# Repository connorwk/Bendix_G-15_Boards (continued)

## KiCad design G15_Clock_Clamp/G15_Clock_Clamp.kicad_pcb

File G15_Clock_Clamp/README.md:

# Clock Clamp, For Bendix G-15 CPU
[Schematic](G15_Clock_Clamp_Schematic.pdf)

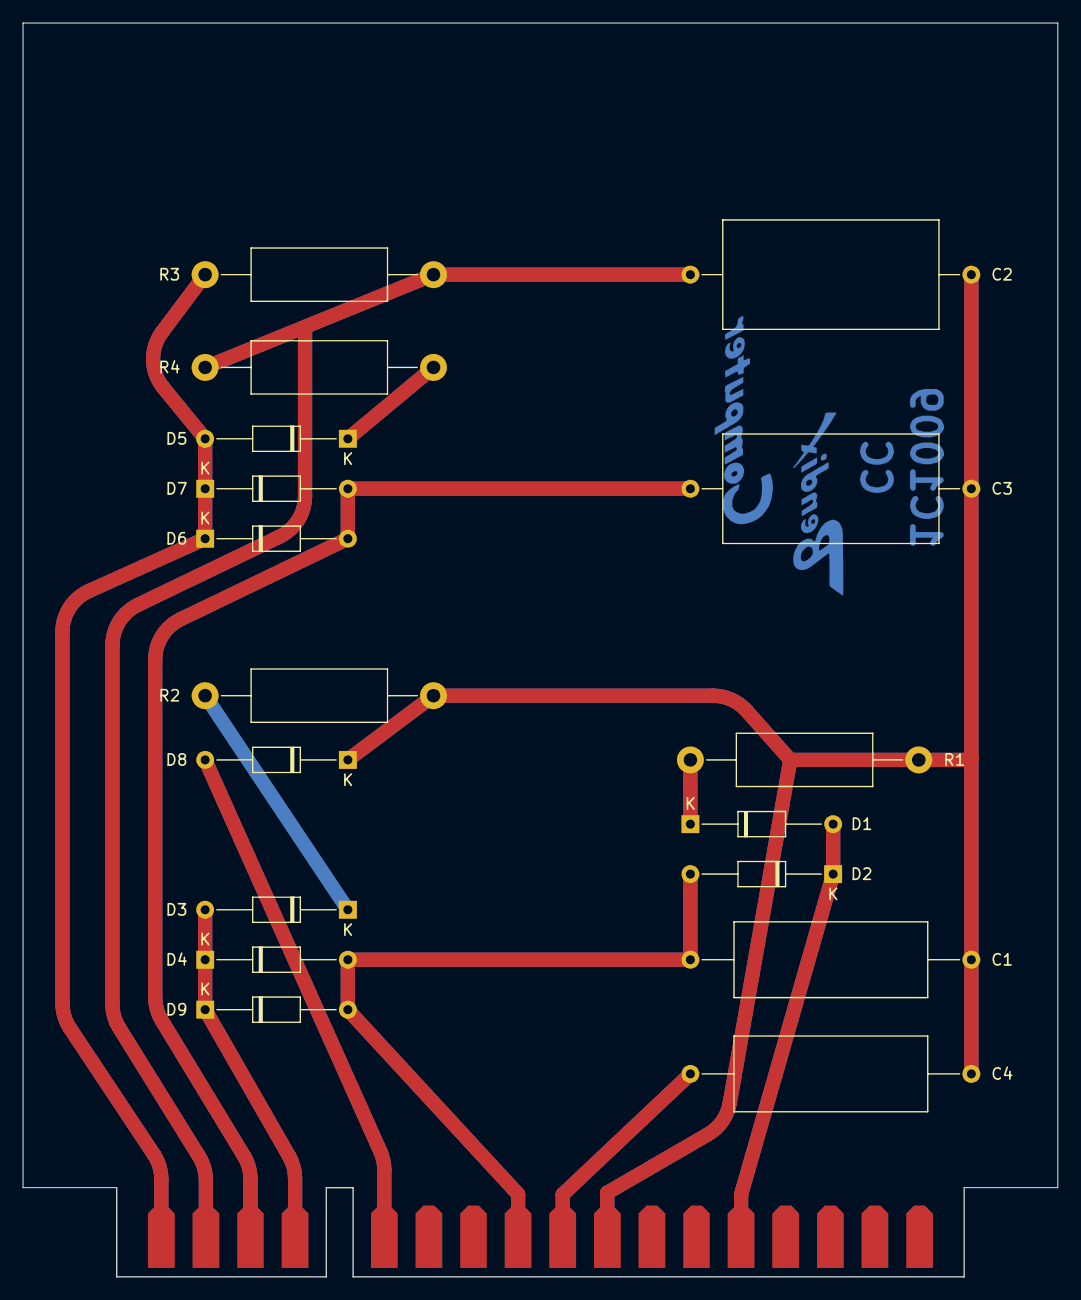
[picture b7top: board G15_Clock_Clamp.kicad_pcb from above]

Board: 2 copper layers, 92.1 x 111.6 mm, 18 parts (0 on the bottom side), 12 nets.

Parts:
C1, C4: 4µF; C_Axial_L17.0mm_D6.5mm_P25.00mm_Horizontal
C2, C3: 0.1µF 200V; C_Axial_L19.0mm_D9.5mm_P25.00mm_Horizontal
D1, D3, D5: 1N4007; D_DO-35_SOD27_P12.70mm_Horizontal
D2, D4, D6, D7, D8, D9: 1N4007_{2}; D_DO-35_SOD27_P12.70mm_Horizontal
J1: Conn_02x18_Row_Letter_First; Card_Edge_R_Key
R1, R2, R4: 33Ω 1W 5%; R_Axial_DIN0414_L11.9mm_D4.5mm_P20.32mm_Horizontal
R3: 390Ω 1W 5%; R_Axial_DIN0414_L11.9mm_D4.5mm_P20.32mm_Horizontal

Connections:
/*-25V: C2.1, J1.a17, J1.b17, R3.1, R4.1
/*-75V: C3.1, D6.2 (A), D7.2 (A), J1.a16, J1.b16
/-13V: C1.1, D2.2 (A), D4.2 (A), D9.2 (A), J1.a10, J1.b10
/-20V: C4.1, J1.a9, J1.b9
/Clock Pulse: D1.2 (A), D2.1 (K), J1.a5, J1.b5
/Read Pulse: D5.2 (A), D6.1 (K), D7.1 (K), J1.a18, J1.b18, R3.2
/Shift Pulse: D3.2 (A), D4.1 (K), D9.1 (K), J1.a15, J1.b15
/Write Pulse: D8.2 (A), J1.a13, J1.b13
GND: C1.2, C2.2, C3.2, C4.2, D8.1 (K), J1.a8, J1.b8, R1.1, R2.1
unnamed: D1.1 (K), R1.2
unnamed: D3.1 (K), R2.2
unnamed: D5.1 (K), R4.2

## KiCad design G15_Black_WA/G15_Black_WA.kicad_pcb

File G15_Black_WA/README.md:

# Write Amplifier, Black Handle, For Bendix G-15 CPU
[Schematic](G15_Black_WA_Schematic.pdf)

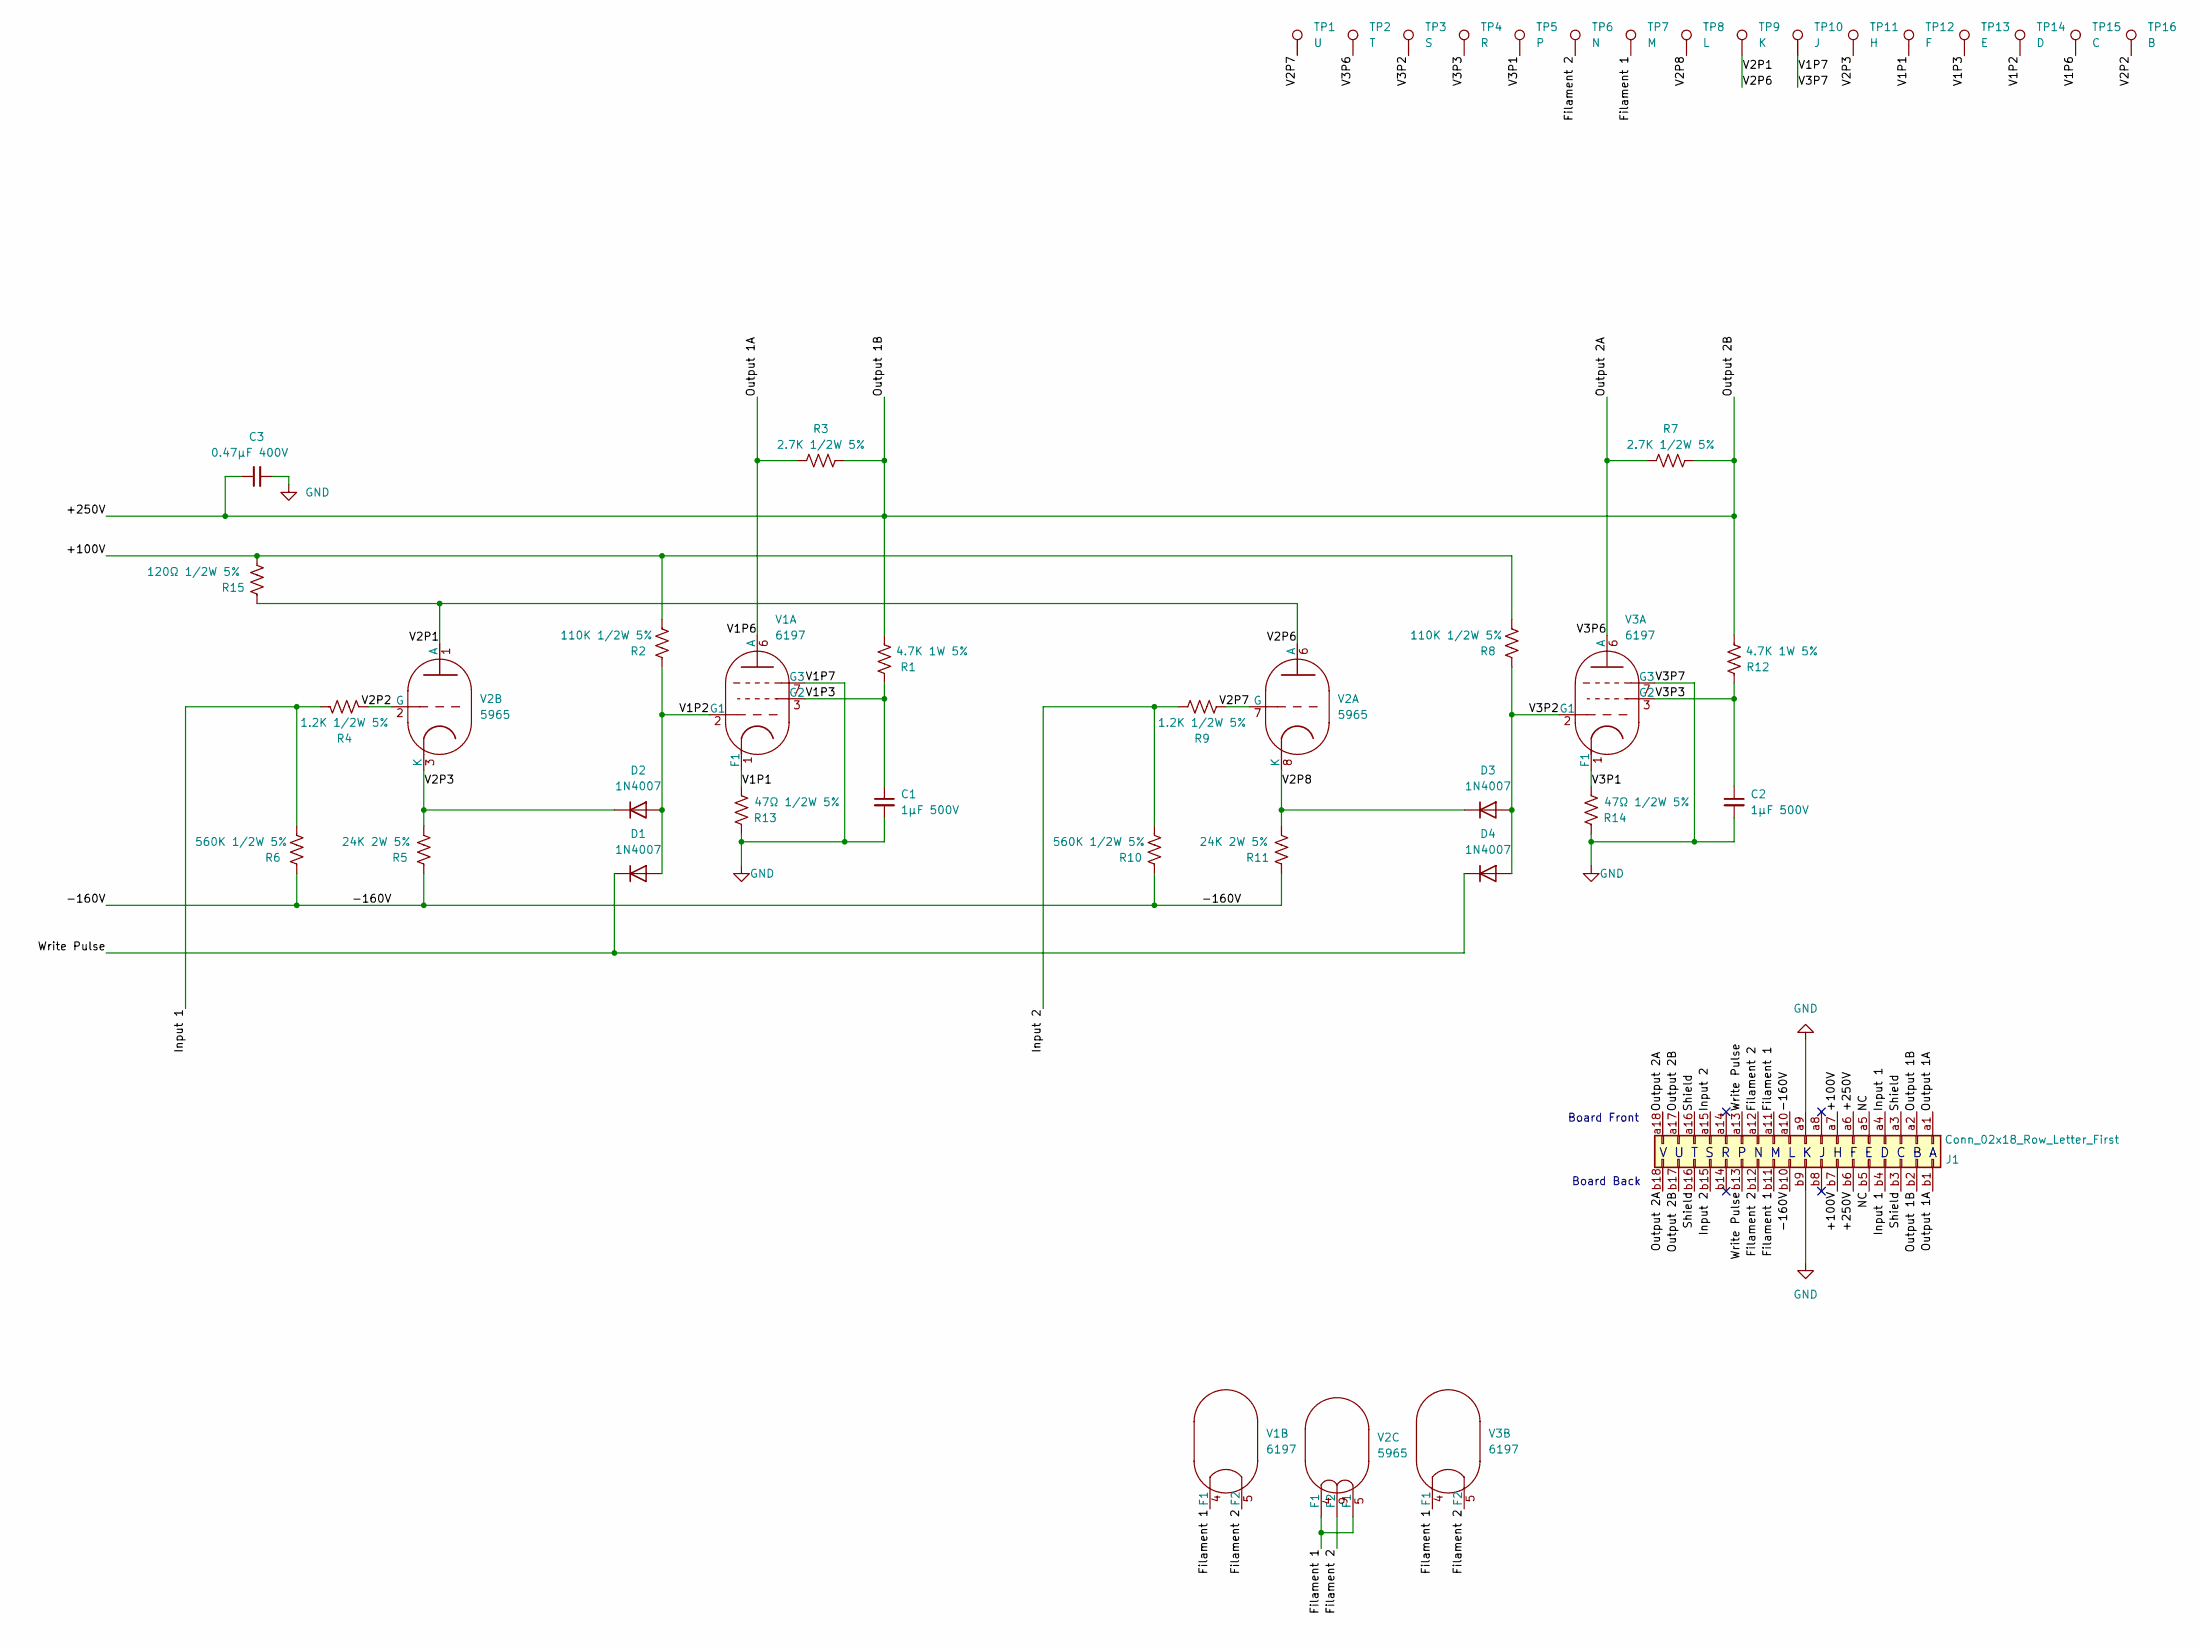
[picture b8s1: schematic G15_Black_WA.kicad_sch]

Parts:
C1, C2: 1µF 500V; C_Axial_L12.0mm_D6.5mm_P20.00mm_Horizontal
C3: 0.47µF 400V; C_Axial_L22.0mm_D10.5mm_P27.50mm_Horizontal
D1, D2, D3, D4: 1N4007; D_DO-35_SOD27_P12.70mm_Horizontal
J1: Conn_02x18_Row_Letter_First; Card_Edge_E_Key
R1, R12: 4.7K 1W 5%; R_Axial_DIN0516_L15.5mm_D5.0mm_P20.32mm_Horizontal
R2, R8: 110K 1/2W 5%; R_Axial_DIN0411_L9.9mm_D3.6mm_P20.32mm_Horizontal
R3, R7: 2.7K 1/2W 5%; R_Axial_DIN0516_L15.5mm_D5.0mm_P20.32mm_Horizontal
R4, R9: 1.2K 1/2W 5%; R_Axial_DIN0411_L9.9mm_D3.6mm_P15.24mm_Horizontal
R5, R11: 24K 2W 5%; R_Axial_DIN0617_L17.0mm_D6.0mm_P25.40mm_Horizontal
R6, R10: 560K 1/2W 5%; R_Axial_DIN0411_L9.9mm_D3.6mm_P15.24mm_Horizontal
R13, R14: 47Ω 1/2W 5%; R_Axial_DIN0411_L9.9mm_D3.6mm_P15.24mm_Horizontal
R15: 120Ω 1/2W 5%; R_Axial_DIN0411_L9.9mm_D3.6mm_P15.24mm_Horizontal
TP1: U; TestPoint_Plated_Hole_D2.0mm
TP2: T; TestPoint_Plated_Hole_D2.0mm
TP3: S; TestPoint_Plated_Hole_D2.0mm
TP4: R; TestPoint_Plated_Hole_D2.0mm
TP5: P; TestPoint_Plated_Hole_D2.0mm
TP6: N; TestPoint_Plated_Hole_D2.0mm
TP7: M; TestPoint_Plated_Hole_D2.0mm
TP8: L; TestPoint_Plated_Hole_D2.0mm
TP9: K; TestPoint_Plated_Hole_D2.0mm
TP10: J; TestPoint_Plated_Hole_D2.0mm
TP11: H; TestPoint_Plated_Hole_D2.0mm
TP12: F; TestPoint_Plated_Hole_D2.0mm
TP13: E; TestPoint_Plated_Hole_D2.0mm
TP14: D; TestPoint_Plated_Hole_D2.0mm
TP15: C; TestPoint_Plated_Hole_D2.0mm
TP16: B; TestPoint_Plated_Hole_D2.0mm
V1, V3: 6197
V2: 5965

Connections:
/+100V: J1.a7, J1.b7, R2.2, R8.2, R15.2
/+250V: C3.1, J1.a2, J1.a6, J1.a17, J1.b2, J1.b6, J1.b17, R1.2, R3.2, R7.2, R12.2
/-160V: J1.a10, J1.b10, R5.1, R6.1, R10.1, R11.1
/Filament 1: J1.a11, J1.b11, TP7.1, V1.4 (F1), V2.4 (F1), V2.5 (F1), V3.4 (F1)
/Filament 2: J1.a12, J1.b12, TP6.1, V1.5 (F2), V2.9 (F2), V3.5 (F2)
/Input 1: J1.a4, J1.b4, R4.1, R6.2
/Input 2: J1.a15, J1.b15, R9.2, R10.2
/Output 1A: J1.a1, J1.b1, R3.1, TP15.1, V1.6 (S)
/Output 2A: J1.a18, J1.b18, R7.1, TP2.1, V3.6 (S)
/Shield: J1.a3, J1.a16, J1.b3, J1.b16
/V1P1: R13.2, TP12.1, V1.1 (F1)
/V1P2: D1.2 (A), D2.2 (A), R2.1, TP14.1, V1.2 (G1)
/V1P3: C1.1, R1.1, TP13.1, V1.3 (F1)
/V2P1: R15.1, TP9.1, V2.1 (A), V2.6 (A)
/V2P2: R4.2, TP16.1, V2.2 (G)
/V2P3: D2.1 (K), R5.2, TP11.1, V2.3 (K)
/V2P7: R9.1, TP1.1, V2.7 (G)
/V2P8: D3.1 (K), R11.2, TP8.1, V2.8 (K)
/V3P1: R14.2, TP5.1, V3.1 (F1)
/V3P2: D3.2 (A), D4.2 (A), R8.1, TP3.1, V3.2 (G1)
/V3P3: C2.1, R12.1, TP4.1, V3.3 (F1)
/Write Pulse: D1.1 (K), D4.1 (K), J1.a13, J1.b13
GND: C1.2, C2.2, C3.2, J1.a9, J1.b9, R13.1, R14.1, TP10.1, V1.7 (A), V3.7 (A)

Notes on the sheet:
Board Back
Board Front
V U T S R P N M L K J H F E D C B A

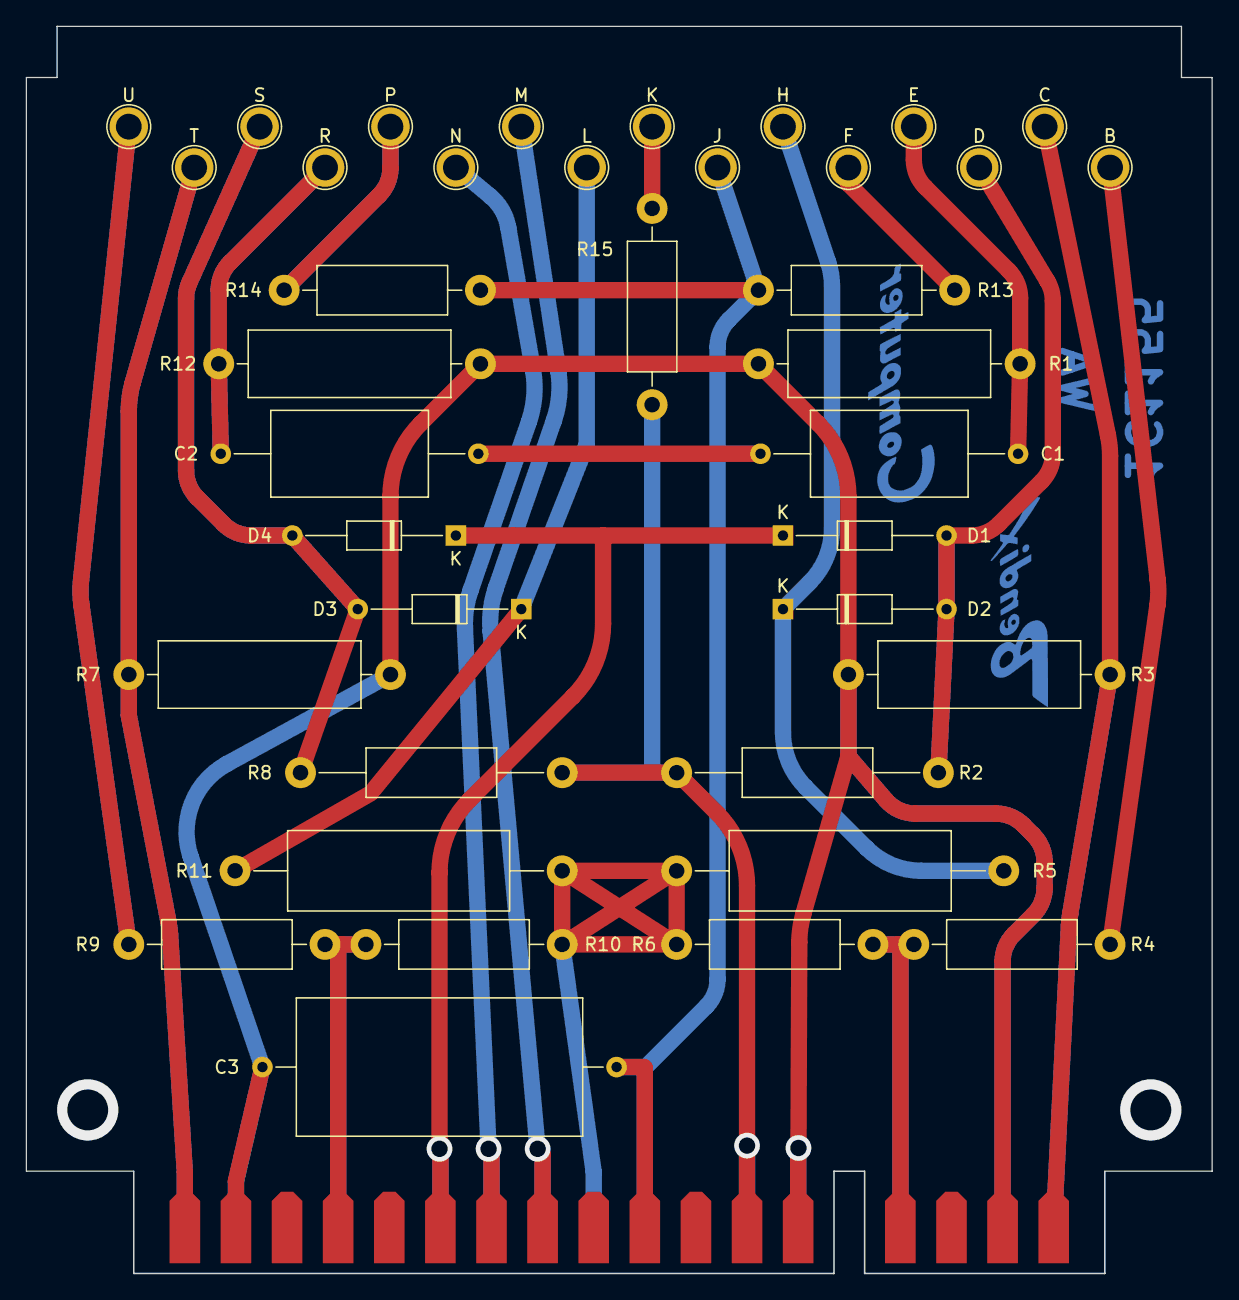
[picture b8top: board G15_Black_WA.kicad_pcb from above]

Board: 2 copper layers, 92.1 x 96.8 mm, 39 parts (0 on the bottom side), 23 nets.

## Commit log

2022-02-02 Initial commit with Gold Flip Flop, Red Cathode Follower 1, and Blue Buffer Inverter
2022-02-02 Rename G15_Blue_BI.md to README.md
2022-02-02 Rename G15_Gold_FF.md to README.md
2022-02-05 Green card Read Amplifier
2022-02-05 Update Readme, add schematic.
2022-02-05 Write Amplifier, Black card, added.
2022-02-05 Update Green Read Amp
2022-02-05 Write Amp schematic
2022-02-17 Cathode Follower 2 board
2022-02-17 Readme update.
2022-02-18 All diode boards.
2022-02-18 Minor updates, and board files.
